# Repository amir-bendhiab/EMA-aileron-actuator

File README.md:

EMA — Actionneur Électromécanique pour Gouverne d'Aileron

Projet portfolio personnel : conception complète d'un actionneur électromécanique (EMA), du cahier des charges jusqu'à l'électronique embarquée — référence d'application : gouverne d'aileron de Pilatus PC-12.

<!-- Ajoutez ici une image de couverture : rendu CAO, ou photo du montage si prototype physique -->
🎯 Contexte

Ce projet couvre le cycle de conception complet d'un actionneur électromécanique linéaire destiné à piloter une gouverne d'aileron : cahier des charges, conception mécanique, modélisation dynamique, commande en boucle fermée, validation par simulation, et conception de l'électronique embarquée.

📐 Spécifications clés
Paramètre	Valeur
Moteur	DC 24V / 300W (ATO-D5BLD300)
Réducteur	Rapport 5:1
Vis à billes	SFU1605
Course	±34,2 mm
Butées mécaniques (linéaire)	±37 mm
Débattement angulaire (gouverne)	+25° / −15° (40° total)
Modèle de charge aérodynamique	T_aero = k·θ (k nominal = 11,73 N·m/deg)
🗂️ Avancement du projet
 Phase 0 — Cahier des charges
 Phase 1 — Conception CAO (SolidWorks)
 Phase 2 — Modélisation électromécanique (Simscape)
 Phase 3 — Commande PID en cascade (courant → vitesse → angle)
 Phase 4 — Validation en simulation
 Phase 5 — Électronique + microcontrôleur (schéma + PCB KiCad)
 Phase 6 — Prototype physique (optionnelle, non prévue dans le cadre de ce projet)
 Phase 7 — Documentation finale (en cours)
🔧 Détail des phases
Phases 1-2 — CAO & Modélisation

Conception mécanique complète sous SolidWorks, puis modélisation électromécanique du système sous Simscape (MATLAB/Simulink) pour disposer d'un modèle dynamique fidèle avant de synthétiser la commande.

Phase 1 (révision) — Butée mécanique angulaire
<!-- Ajoutez ici une capture de la liaison d'angle avec limites dans SolidWorks -->

Après validation de la commande en simulation (Phase 4), retour sur la CAO pour traduire la plage validée en contrainte mécanique cohérente : une liaison d'angle avec limites (+25° / −15°) sur l'axe de charnière — seul élément de la chaîne cinématique dont la rotation reste fixe dans l'espace, donc le seul candidat pertinent pour une butée directe.

La chaîne cinématique complète a été reconstruite et validée dans SolidWorks avec les liaisons mécaniques appropriées : liaison Pignon (couplage rigide réducteur → vis à billes via l'accouplement) et liaison Vis (conversion rotation → translation, pas de 5mm) pour la vis à billes. Une seconde liaison d'angle, en marge de sécurité, protège le bras de levier contre les configurations géométriques non réalistes (le bras combinant rotation et translation, sans butée physique propre dans la réalité).

Phase 3 — Commande

Architecture de commande en cascade à trois boucles imbriquées : courant → vitesse → angle, chacune réglée successivement de l'intérieur vers l'extérieur.

Phase 4 — Validation en simulation

Tests par échelons (+25° / −15°) face à un modèle de charge aérodynamique. Un point notable du processus : la limitation de courant initiale (±5A) empêchait l'actionneur d'atteindre l'angle cible en butée de saturation — corrigée à ±12A après vérification du courant nominal réel du moteur. Un test de robustesse complémentaire (doublement de la raideur de charge aérodynamique k) a confirmé la tenue du système face à une charge plus sévère que le cas nominal.

Phase 5 — Électronique (schéma + PCB)

Conception complète sous KiCad :

Alimentation : 28V → 5V (LM2596S) → 3,3V (AMS1117), régulation à deux étages
Driver moteur : BTS7960 (pont en H)
Mesure de courant : INA240 + shunt 0,01Ω, dimensionné pour ~14A avec marge de sécurité
Retour de position : encodeur magnétique absolu AS5048A (interface SPI)
Microcontrôleur : STM32F401RETx

Schéma validé (ERC : 0 erreur). PCB 120×80mm entièrement routé et validé (DRC : 0 violation, 0 connexion manquante), avec 5 zones de cuivre dédiées à la puissance (+28V, GND double face, retour moteur).

Limitation connue : les pistes de puissance sont restées à la largeur standard (0,25mm) plutôt que la largeur calculée pour ~14A (8mm), documentée directement sur le PCB. Choix assumé : ce PCB est un exercice de conception, non destiné à la fabrication physique dans le cadre de ce projet.

🛠️ Stack technique
CAO : SolidWorks
Simulation & Commande : MATLAB/Simulink, Simscape
Électronique : KiCad
Microcontrôleur cible : STM32F401RETx
🚀 Suite du projet
Développement du firmware embarqué (implémentation temps réel de la boucle de commande sur STM32)
Documentation finale consolidée
👤 À propos

Projet réalisé par Amir Ben Dhiab, étudiant ingénieur en Génie Électromécanique (spécialisation Robotique & IA) à l'École Polytechnique de Sousse (EPS), Tunisie — dans le cadre de la préparation aux candidatures de stage de fin d'études (PFE), février 2027.

🔗 github.com/amir-bendhiab

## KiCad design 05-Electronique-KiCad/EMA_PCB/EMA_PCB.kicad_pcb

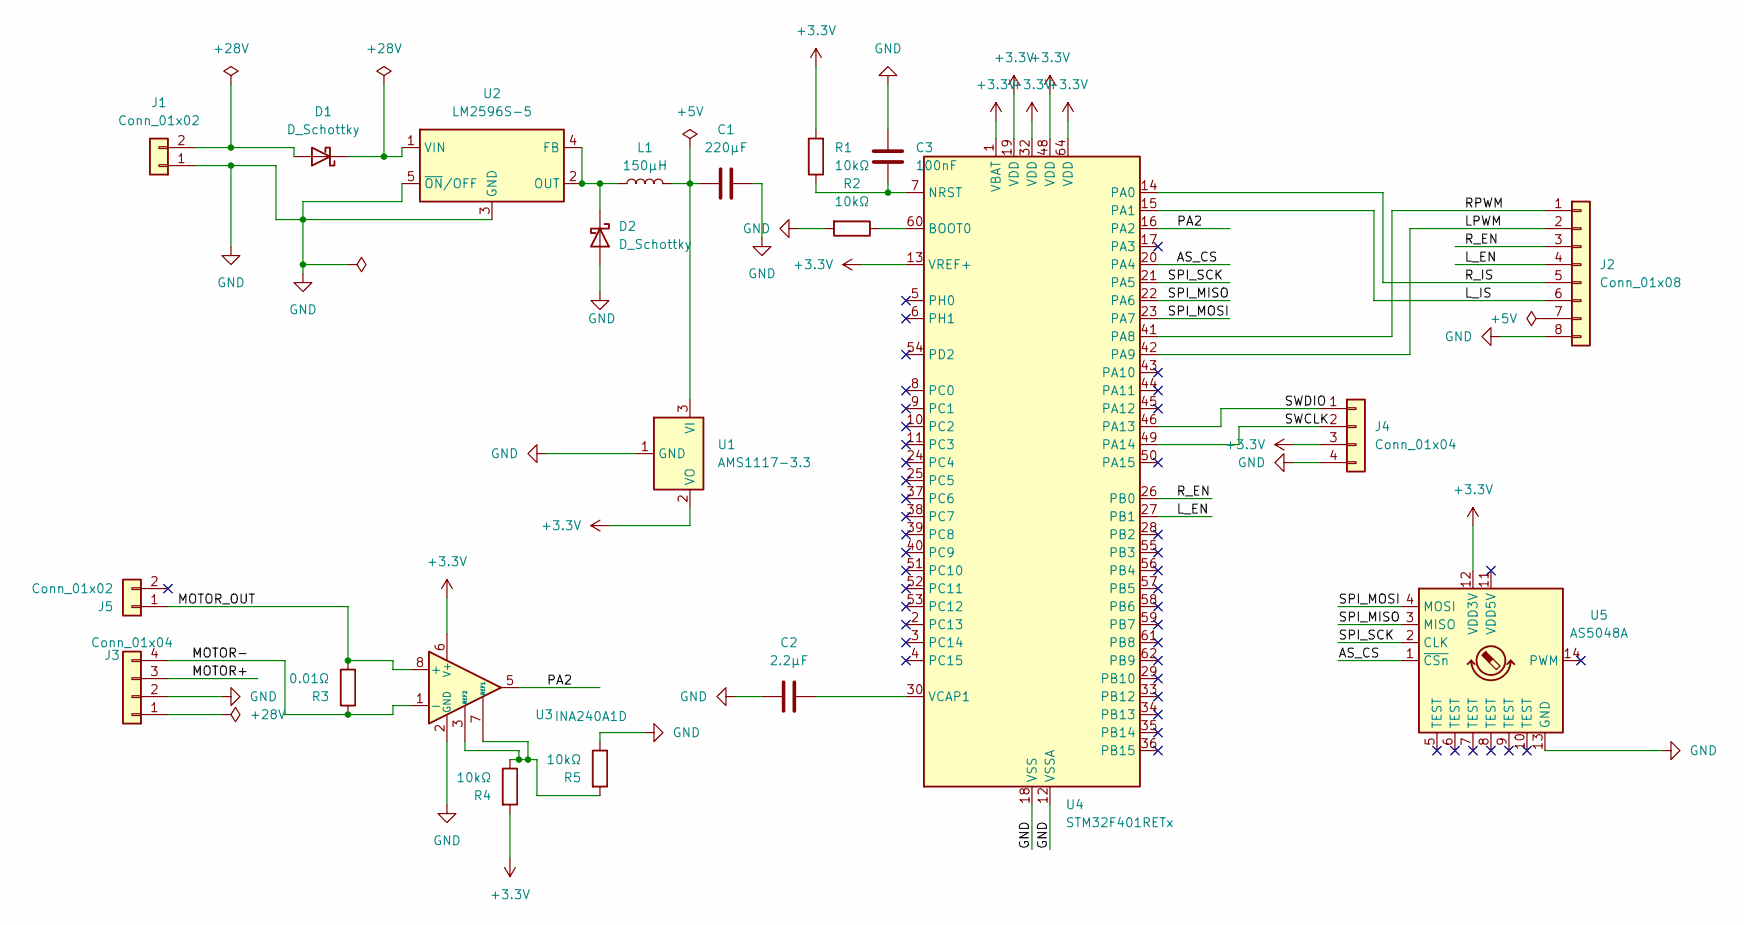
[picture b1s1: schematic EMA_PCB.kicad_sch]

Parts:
C1: 220µF; CP_Radial_D8.0mm_P3.50mm
C2: 2.2µF; C_0805_2012Metric
C3: 100nF; C_0603_1608Metric
D1, D2: D_Schottky; D_SMA
J1, J5: Conn_01x02; TerminalBlock_CUI_TB007-508-02_1x02_P5.08mm_Horizontal
J2: Conn_01x08; PinHeader_1x08_P2.54mm_Vertical
J3: Conn_01x04; TerminalBlock_CUI_TB007-508-04_1x04_P5.08mm_Horizontal
J4: Conn_01x04; PinHeader_1x04_P2.54mm_Vertical
L1: 150µH; L_Wuerth_WE-TPC-3816
R1, R2, R4, R5: 10kΩ; R_0805_2012Metric
R3: 0.01Ω; R_2512_6332Metric
U1: AMS1117-3.3; SOT-223-3_TabPin2
U2: LM2596S-5; TO-263-5_TabPin3
U3: INA240A1D; SOIC-8_3.9x4.9mm_P1.27mm
U4: STM32F401RETx; LQFP-64_10x10mm_P0.5mm
U5: AS5048A; TSSOP-14_4.4x5mm_P0.65mm

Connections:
+3.3V: J4.3, R1.2, R4.2, U1.2 (VO), U3.6 (V+), U4.1 (VBAT), U4.13 (VREF+), U4.19 (VDD), U4.32 (VDD), U4.48 (VDD), U4.64 (VDD), U5.12 (VDD3V)
/AS_CS: U4.20 (PA4), U5.1 (~CSn)
/LPWM: J2.2, U4.42 (PA9)
/L_EN: J2.4, U4.27 (PB1)
/L_IS: J2.6, U4.15 (PA1)
/MOTOR+: J3.3
/MOTOR-: J3.4, R3.1, U3.1 (-)
/MOTOR_OUT: J5.1 (Pin_1_1), R3.2, U3.8 (+)
/PA2: U3.5, U4.16 (PA2)
/RPWM: J2.1, U4.41 (PA8)
/R_EN: J2.3, U4.26 (PB0)
/R_IS: J2.5, U4.14 (PA0)
/SPI_MISO: U4.22 (PA6), U5.3 (MISO)
/SPI_MOSI: U4.23 (PA7), U5.4 (MOSI)
/SPI_SCK: U4.21 (PA5), U5.2 (CLK)
/SWCLK: J4.2, U4.49 (PA14)
/SWDIO: J4.1, U4.46 (PA13)
GND: C1.2, C2.1, C3.2, D2.2 (A), J1.1, J2.8, J3.2, J4.4, R2.2, R5.1, U1.1 (GND), U2.3 (GND), U2.5 (~ON/OFF), U3.2 (GND), U3.4 (GND), U4.12 (VSSA), U4.18 (VSS), U4.31 (VSS), U4.47 (VSS), U4.63 (VSS), U5.13 (GND)
unnamed: D1.2 (A), J1.2
unnamed: D1.1 (K), U2.1 (VIN)
unnamed: D2.1 (K), L1.1, U2.2 (OUT), U2.4 (FB)
unnamed: C1.1, L1.2, U1.3 (VI)
unnamed: R4.1, R5.2, U3.3 (REF2), U3.7 (REF1)
unnamed: R2.1, U4.60 (BOOT0)
unnamed: C3.1, R1.1, U4.7 (NRST)
unnamed: C2.2, U4.30 (VCAP1)

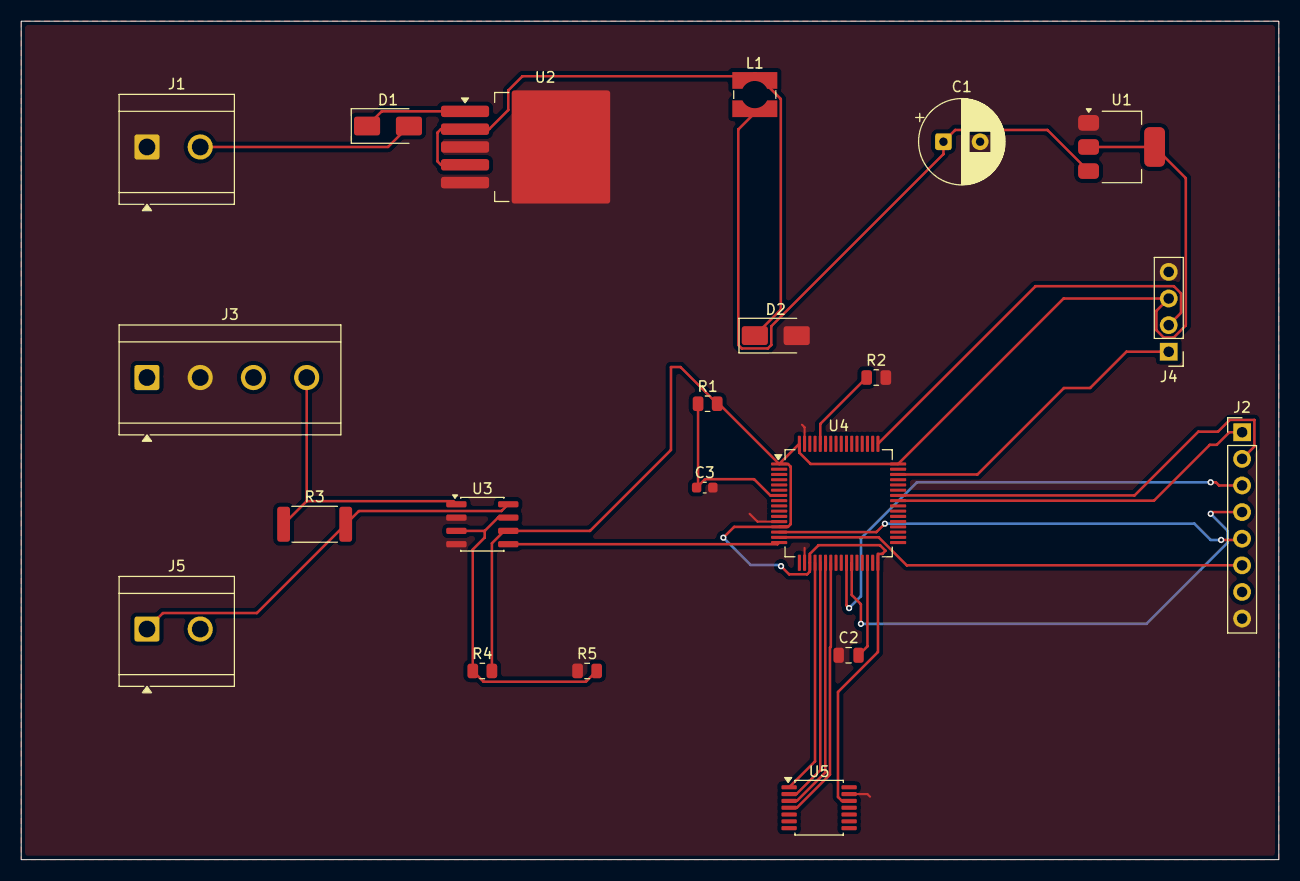
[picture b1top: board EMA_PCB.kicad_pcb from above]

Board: 2 copper layers, 120.0 x 80.0 mm, 21 parts (0 on the bottom side), 25 nets.
